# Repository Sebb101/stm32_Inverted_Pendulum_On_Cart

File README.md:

# Stm32_Inverted_Pendulum_On_Cart
Control systems learning project

Classic controls project: Inverted Pendulum On a Cart

Designed a custom stm32 board to handle data acquisition, motor control, and data out.

Tuned PID constants using matlab's System Identification and PID tuner applications

3D printed motor, encoder mounts, rail fixture and cart.

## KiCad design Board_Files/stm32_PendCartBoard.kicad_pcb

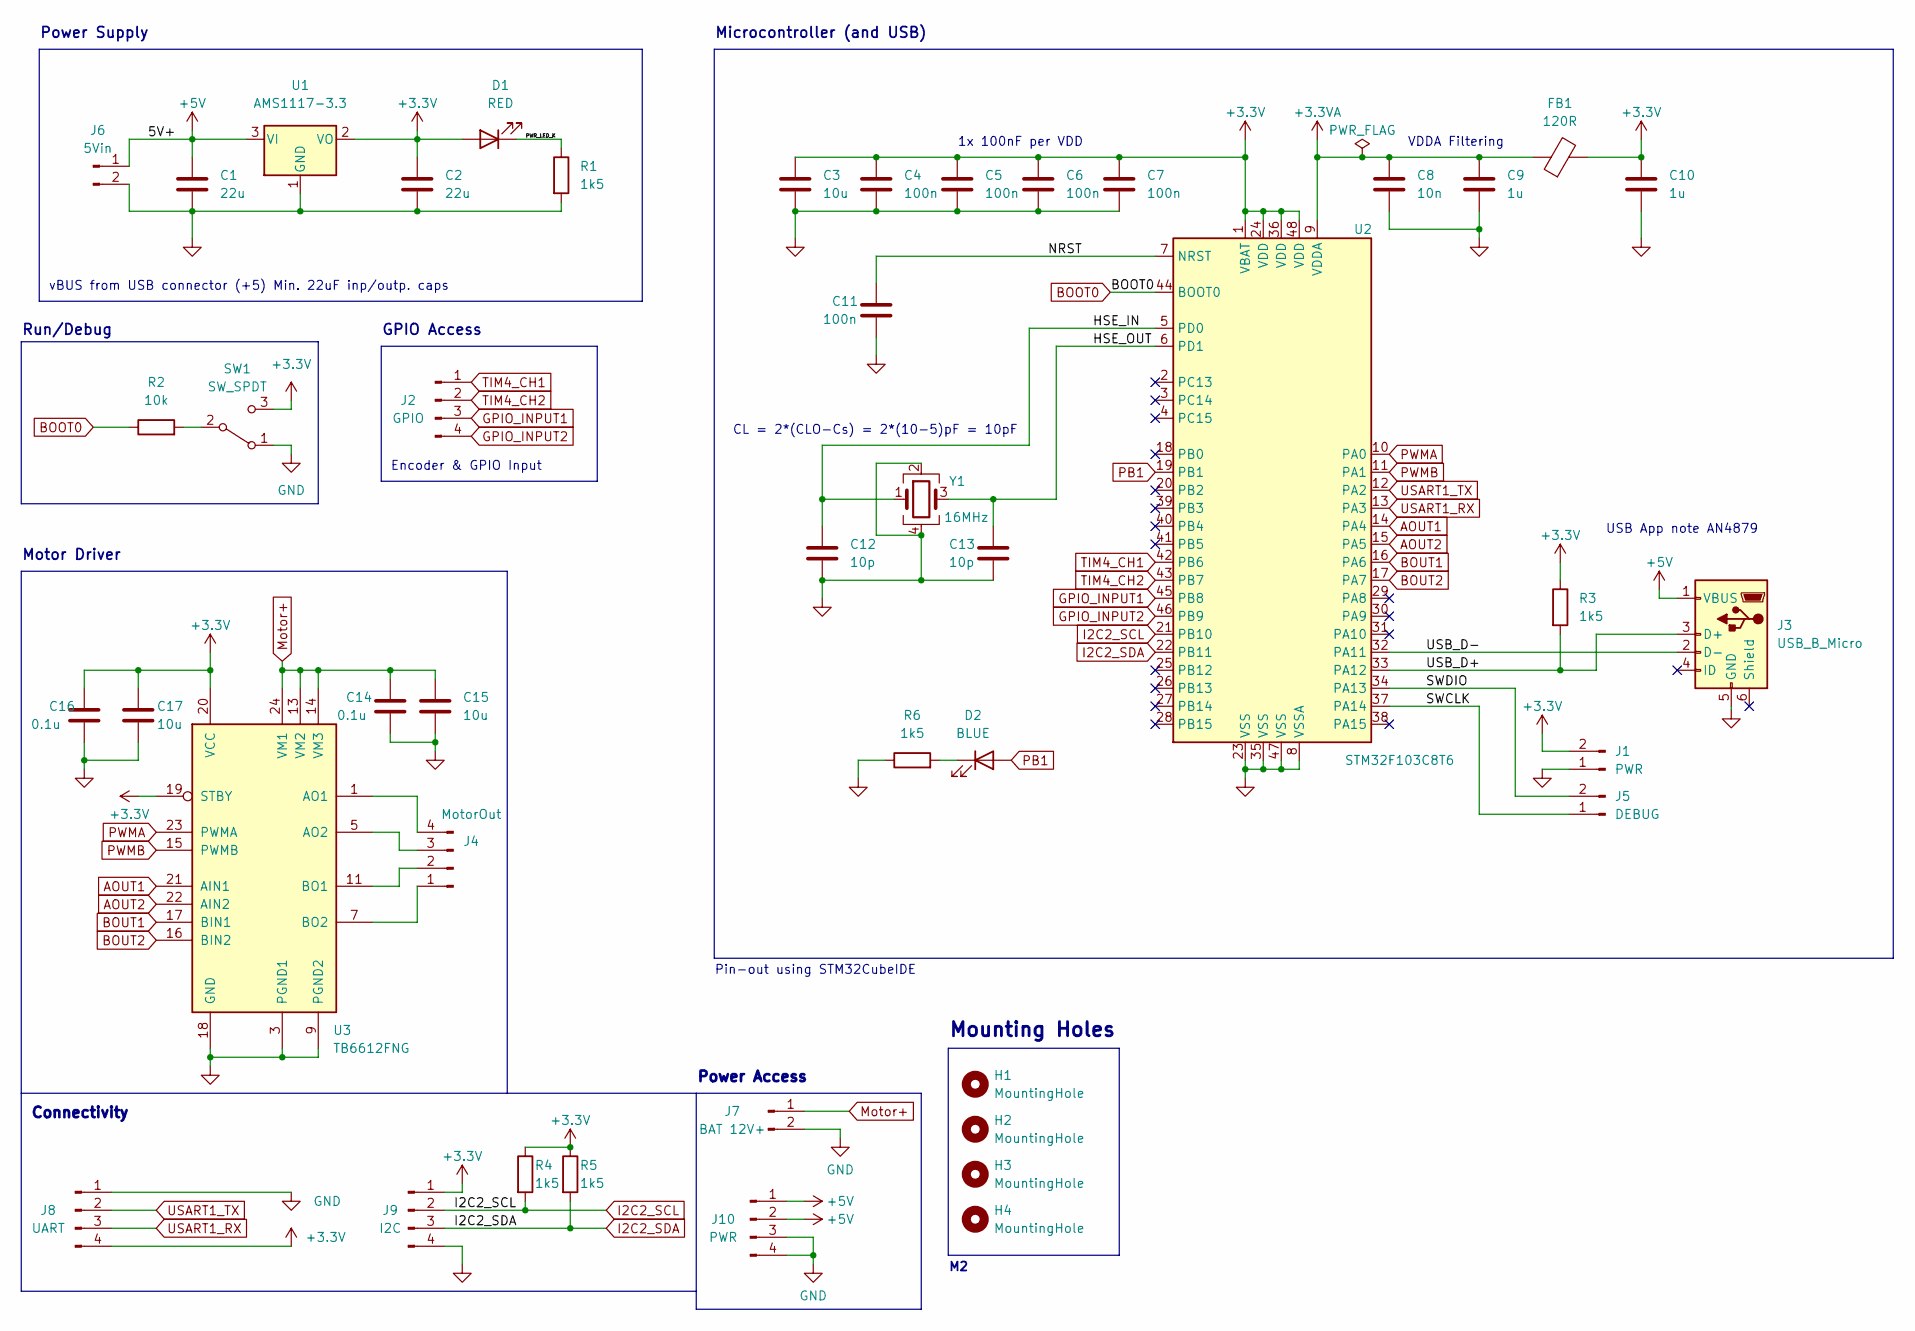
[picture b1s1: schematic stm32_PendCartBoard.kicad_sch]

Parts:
C1, C2: 22u; C_0805_2012Metric
C3: 10u; C_0603_1608Metric
C4, C5, C6, C7, C11: 100n; C_0402_1005Metric
C8: 10n; C_0402_1005Metric
C9, C10: 1u; C_0402_1005Metric
C12, C13: 10p; C_0402_1005Metric
C14, C16: 0.1u; C_0805_2012Metric
C15, C17: 10u; C_0805_2012Metric
D1: RED; LED_0603_1608Metric
D2: BLUE; LED_0603_1608Metric
FB1: 120R; L_0603_1608Metric
H1, H2, H3, H4: MountingHole; MountingHole_2.2mm_M2
J1: PWR; PinHeader_1x02_P2.54mm_Vertical
J2: GPIO; PinHeader_1x04_P2.54mm_Vertical
J3: USB_B_Micro; USB_Micro-B_Wuerth_629105150521
J4: MotorOut; PinHeader_1x04_P2.54mm_Vertical
J5: DEBUG; PinHeader_1x02_P2.54mm_Vertical
J6: 5Vin; PinHeader_1x02_P2.54mm_Vertical
J7: BAT 12V+; PinHeader_1x02_P2.54mm_Vertical
J8: UART; PinHeader_1x04_P2.54mm_Vertical
J9: I2C; PinHeader_1x04_P2.54mm_Vertical
J10: PWR; PinHeader_1x04_P2.54mm_Vertical
R1, R3, R4, R5, R6: 1k5; R_0402_1005Metric
R2: 10k; R_0402_1005Metric
SW1: SW_SPDT; SW_SPDT_PCM12
U1: AMS1117-3.3; SOT-223-3_TabPin2
U2: STM32F103C8T6; LQFP-48_7x7mm_P0.5mm
U3: TB6612FNG; SSOP-24_5.3x8.2mm_P0.65mm
Y1: 16MHz; Crystal_SMD_3225-4Pin_3.2x2.5mm

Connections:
+3.3V: C2.1, C3.1, C4.1, C5.1, C6.1, C7.1, C10.1, C16.1, C17.1, D1.2 (A), FB1.2, J1.2, J8.4, J9.1, R3.1, R4.1, R5.1, SW1.3 (C), U1.2 (VO), U2.1 (VBAT), U2.24 (VDD), U2.36 (VDD), U2.48 (VDD), U3.19 (STBY), U3.20 (VCC)
+3.3VA: C8.1, C9.1, FB1.1, U2.9 (VDDA)
+5V: C1.1, J3.1 (VBUS), J6.1, J10.1, J10.2, U1.3 (VI)
/HSE_IN: C12.1, U2.5 (PD0), Y1.1
/HSE_OUT: C13.1, U2.6 (PD1), Y1.3
/NRST: C11.1, U2.7 (NRST)
/PWR_LED_K: D1.1 (K), R1.1
/SWCLK: J5.1, U2.37 (PA14)
/SWDIO: J5.2, U2.34 (PA13)
/USB_D+: J3.3 (D+), R3.2, U2.33 (PA12)
/USB_D-: J3.2 (D-), U2.32 (PA11)
AOUT1: U2.14 (PA4), U3.21 (AIN1)
AOUT2: U2.15 (PA5), U3.22 (AIN2)
BOOT0: R2.1, U2.44 (BOOT0)
BOUT1: U2.16 (PA6), U3.17 (BIN1)
BOUT2: U2.17 (PA7), U3.16 (BIN2)
GND: C1.2, C2.2, C3.2, C4.2, C5.2, C6.2, C7.2, C8.2, C9.2, C10.2, C11.2, C12.2, C13.2, C14.2, C15.2, C16.2, C17.2, J1.1, J3.5 (GND), J6.2, J7.2, J8.1, J9.4, J10.3, J10.4, R1.2, R6.1, SW1.1 (A), U1.1 (GND), U2.8 (VSSA), U2.23 (VSS), U2.35 (VSS), U2.47 (VSS), U3.3 (PGND1), U3.4 (PGND1), U3.9 (PGND2), U3.10 (PGND2), U3.18 (GND), Y1.2, Y1.4
GPIO_INPUT1: J2.3, U2.45 (PB8)
GPIO_INPUT2: J2.4, U2.46 (PB9)
I2C2_SCL: J9.2, R4.2, U2.21 (PB10)
I2C2_SDA: J9.3, R5.2, U2.22 (PB11)
Motor+: C14.1, C15.1, J7.1, U3.13 (VM2), U3.14 (VM3), U3.24 (VM1)
unnamed: D2.1 (K), R6.2
unnamed: J4.1, U3.7 (BO2), U3.8 (BO2)
unnamed: J4.2, U3.11 (BO1), U3.12 (BO1)
unnamed: J4.3, U3.5 (AO2), U3.6 (AO2)
unnamed: J4.4, U3.1 (AO1), U3.2 (AO1)
unnamed: R2.2, SW1.2 (B)
PB1: D2.2 (A), U2.19 (PB1)
PWMA: U2.10 (PA0), U3.23 (PWMA)
PWMB: U2.11 (PA1), U3.15 (PWMB)
TIM4_CH1: J2.1, U2.42 (PB6)
TIM4_CH2: J2.2, U2.43 (PB7)
USART1_RX: J8.3, U2.13 (PA3)
USART1_TX: J8.2, U2.12 (PA2)

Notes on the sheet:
Microcontroller (and USB)
VDDA Filtering
Motor Driver
Mounting Holes
GPIO Access
Power Access
Connectivity
Pin-out using STM32CubeIDE
Run/Debug
Encoder & GPIO Input
1x 100nF per VDD
USB App note AN4879
Power Supply
CL = 2*(CLO-Cs) = 2*(10-5)pF = 10pF
vBUS from USB connector (+5) Min. 22uF inp/outp. caps

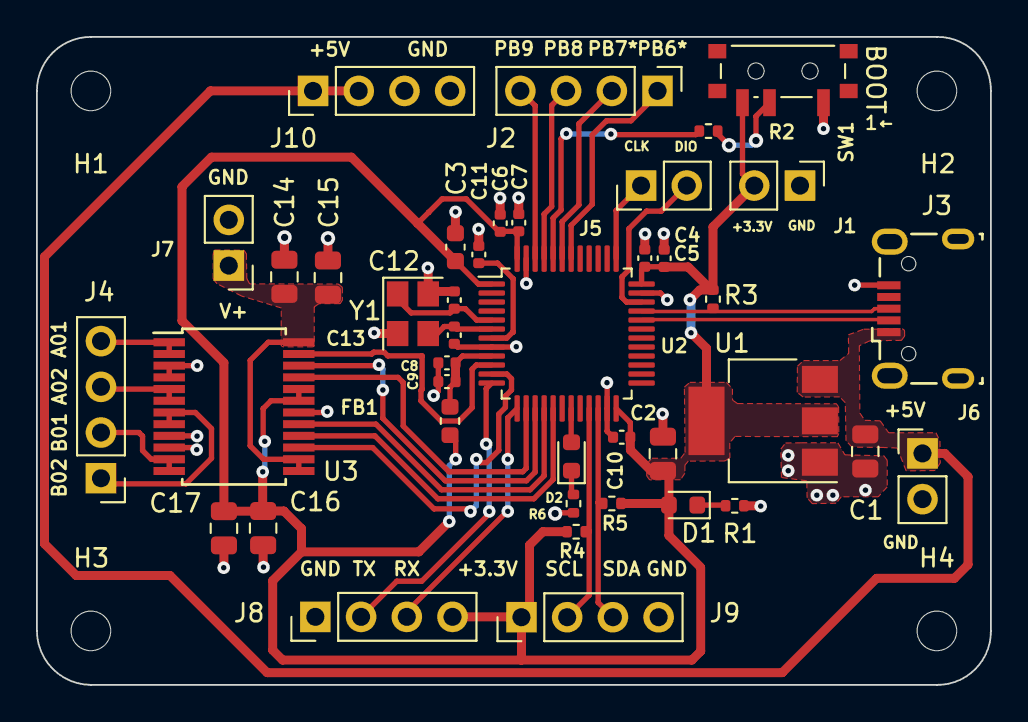
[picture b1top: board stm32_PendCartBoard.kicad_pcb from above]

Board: 2 copper layers, 53.0 x 36.0 mm, 45 parts (0 on the bottom side), 35 nets.

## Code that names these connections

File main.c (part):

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  /* USER CODE BEGIN WHILE */
  while (1)
  {
	  // Test board LED PB1
	  //HAL_GPIO_WritePin(GPIOB, GPIO_PIN_1, 1);
	  //HAL_Delay(1000);
	  //HAL_GPIO_WritePin(GPIOB, GPIO_PIN_1, 0);
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  /*Configure GPIO pin Output Level */
  HAL_GPIO_WritePin(GPIOB, GPIO_PIN_1, GPIO_PIN_RESET);

  /*Configure GPIO pins : PA4 PA5 PA6 PA7 */
  GPIO_InitStruct.Pin = GPIO_PIN_4|GPIO_PIN_5|GPIO_PIN_6|GPIO_PIN_7;
  GPIO_InitStruct.Mode = GPIO_MODE_OUTPUT_PP;
  GPIO_InitStruct.Pull = GPIO_NOPULL;
  GPIO_InitStruct.Speed = GPIO_SPEED_FREQ_LOW;
  HAL_GPIO_Init(GPIOA, &GPIO_InitStruct);

  /*Configure GPIO pin : PB1 */
  GPIO_InitStruct.Pin = GPIO_PIN_1;
  GPIO_InitStruct.Mode = GPIO_MODE_OUTPUT_PP;
  GPIO_InitStruct.Pull = GPIO_NOPULL;
  GPIO_InitStruct.Speed = GPIO_SPEED_FREQ_LOW;
  HAL_GPIO_Init(GPIOB, &GPIO_InitStruct);

  /*Configure GPIO pin : PB8 */
  GPIO_InitStruct.Pin = GPIO_PIN_8;
  GPIO_InitStruct.Mode = GPIO_MODE_IT_RISING;
  GPIO_InitStruct.Pull = GPIO_NOPULL;
  HAL_GPIO_Init(GPIOB, &GPIO_InitStruct);

  /*Configure GPIO pin : PB9 */
  GPIO_InitStruct.Pin = GPIO_PIN_9;
  GPIO_InitStruct.Mode = GPIO_MODE_INPUT;
  GPIO_InitStruct.Pull = GPIO_NOPULL;
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
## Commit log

2024-12-24 Create misc.txt
    meep

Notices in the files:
main.c:
Copyright (c) 2023 STMicroelectronics.
All rights reserved.
This software is licensed under terms that can be found in the LICENSE file
